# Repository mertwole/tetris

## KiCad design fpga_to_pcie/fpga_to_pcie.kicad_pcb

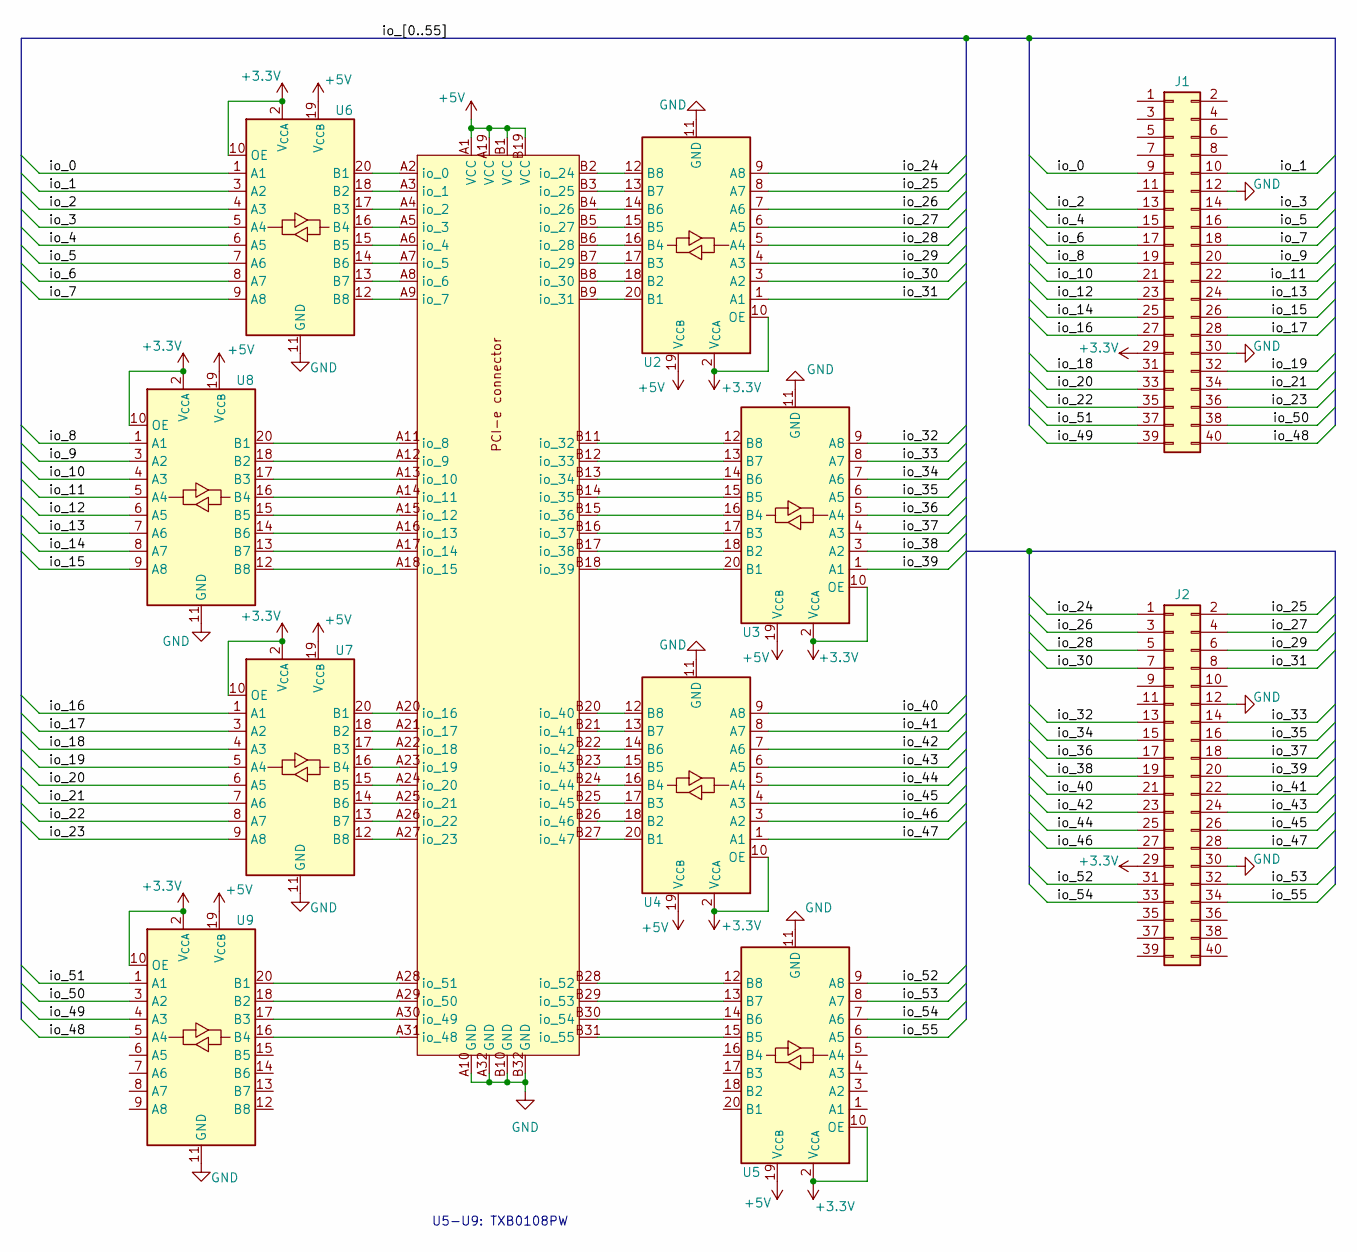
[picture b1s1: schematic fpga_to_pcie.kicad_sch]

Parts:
J1, J2: Conn_02x20_Odd_Even; IDC-Header_2x20_P2.54mm_Vertical
U1: BUS_PCIexpress_x4
U2, U3, U4, U5, U6, U7, U8, U9: TXB0108PW; TSSOP-20_4.4x6.5mm_P0.65mm

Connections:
+3.3V: J1.29, J2.29, U2.2 (V_{CCA}), U2.10 (OE), U3.2 (V_{CCA}), U3.10 (OE), U4.2 (V_{CCA}), U4.10 (OE), U5.2 (V_{CCA}), U5.10 (OE), U6.2 (V_{CCA}), U6.10 (OE), U7.2 (V_{CCA}), U7.10 (OE), U8.2 (V_{CCA}), U8.10 (OE), U9.2 (V_{CCA}), U9.10 (OE)
+5V: U1.A1 (VCC), U1.A19 (VCC), U1.B1 (VCC), U1.B19 (VCC), U2.19 (V_{CCB}), U3.19 (V_{CCB}), U4.19 (V_{CCB}), U5.19 (V_{CCB}), U6.19 (V_{CCB}), U7.19 (V_{CCB}), U8.19 (V_{CCB}), U9.19 (V_{CCB})
/io_0: J1.9, U6.1 (A1)
/io_1: J1.10, U6.3 (A2)
/io_2: J1.13, U6.4 (A3)
/io_3: J1.14, U6.5 (A4)
/io_4: J1.15, U6.6 (A5)
/io_5: J1.16, U6.7 (A6)
/io_6: J1.17, U6.8 (A7)
/io_7: J1.18, U6.9 (A8)
/io_8: J1.19, U8.1 (A1)
/io_9: J1.20, U8.3 (A2)
/io_10: J1.21, U8.4 (A3)
/io_11: J1.22, U8.5 (A4)
/io_12: J1.23, U8.6 (A5)
/io_13: J1.24, U8.7 (A6)
/io_14: J1.25, U8.8 (A7)
/io_15: J1.26, U8.9 (A8)
/io_16: J1.27, U7.1 (A1)
/io_17: J1.28, U7.3 (A2)
/io_18: J1.31, U7.4 (A3)
/io_19: J1.32, U7.5 (A4)
/io_20: J1.33, U7.6 (A5)
/io_21: J1.34, U7.7 (A6)
/io_22: J1.35, U7.8 (A7)
/io_23: J1.36, U7.9 (A8)
/io_24: J2.1, U2.9 (A8)
/io_25: J2.2, U2.8 (A7)
/io_26: J2.3, U2.7 (A6)
/io_27: J2.4, U2.6 (A5)
/io_28: J2.5, U2.5 (A4)
/io_29: J2.6, U2.4 (A3)
/io_30: J2.7, U2.3 (A2)
/io_31: J2.8, U2.1 (A1)
/io_32: J2.13, U3.9 (A8)
/io_33: J2.14, U3.8 (A7)
/io_34: J2.15, U3.7 (A6)
/io_35: J2.16, U3.6 (A5)
/io_36: J2.17, U3.5 (A4)
/io_37: J2.18, U3.4 (A3)
/io_38: J2.19, U3.3 (A2)
/io_39: J2.20, U3.1 (A1)
/io_40: J2.21, U4.9 (A8)
/io_41: J2.22, U4.8 (A7)
/io_42: J2.23, U4.7 (A6)
/io_43: J2.24, U4.6 (A5)
/io_44: J2.25, U4.5 (A4)
/io_45: J2.26, U4.4 (A3)
/io_46: J2.27, U4.3 (A2)
/io_47: J2.28, U4.1 (A1)
/io_48: J1.40, U9.5 (A4)
/io_49: J1.39, U9.4 (A3)
/io_50: J1.38, U9.3 (A2)
/io_51: J1.37, U9.1 (A1)
/io_52: J2.31, U5.9 (A8)
/io_53: J2.32, U5.8 (A7)
/io_54: J2.33, U5.7 (A6)
/io_55: J2.34, U5.6 (A5)
GND: J1.12, J1.30, J2.12, J2.30, U1.A10 (GND), U1.A32 (GND), U1.B10 (GND), U1.B32 (GND), U2.11 (GND), U3.11 (GND), U4.11 (GND), U5.11 (GND), U6.11 (GND), U7.11 (GND), U8.11 (GND), U9.11 (GND)
unnamed: U1.A2 (io_0), U6.20 (B1)
unnamed: U1.A3 (io_1), U6.18 (B2)
unnamed: U1.A4 (io_2), U6.17 (B3)
unnamed: U1.A5 (io_3), U6.16 (B4)
unnamed: U1.A6 (io_4), U6.15 (B5)
unnamed: U1.A7 (io_5), U6.14 (B6)
unnamed: U1.A8 (io_6), U6.13 (B7)
unnamed: U1.A9 (io_7), U6.12 (B8)
unnamed: U1.A11 (io_8), U8.20 (B1)
unnamed: U1.A12 (io_9), U8.18 (B2)
unnamed: U1.A13 (io_10), U8.17 (B3)
unnamed: U1.A14 (io_11), U8.16 (B4)
unnamed: U1.A15 (io_12), U8.15 (B5)
unnamed: U1.A16 (io_13), U8.14 (B6)
unnamed: U1.A17 (io_14), U8.13 (B7)
unnamed: U1.A18 (io_15), U8.12 (B8)
unnamed: U1.A20 (io_16), U7.20 (B1)
unnamed: U1.A21 (io_17), U7.18 (B2)
unnamed: U1.A22 (io_18), U7.17 (B3)
unnamed: U1.A23 (io_19), U7.16 (B4)
unnamed: U1.A24 (io_20), U7.15 (B5)
unnamed: U1.A25 (io_21), U7.14 (B6)
unnamed: U1.A26 (io_22), U7.13 (B7)
unnamed: U1.A27 (io_23), U7.12 (B8)
unnamed: U1.B2 (io_24), U2.12 (B8)
unnamed: U1.B3 (io_25), U2.13 (B7)
unnamed: U1.B4 (io_26), U2.14 (B6)
unnamed: U1.B5 (io_27), U2.15 (B5)
unnamed: U1.B6 (io_28), U2.16 (B4)
unnamed: U1.B7 (io_29), U2.17 (B3)
unnamed: U1.B8 (io_30), U2.18 (B2)
unnamed: U1.B9 (io_31), U2.20 (B1)
unnamed: U1.B11 (io_32), U3.12 (B8)
unnamed: U1.B12 (io_33), U3.13 (B7)
unnamed: U1.B13 (io_34), U3.14 (B6)
unnamed: U1.B14 (io_35), U3.15 (B5)
unnamed: U1.B15 (io_36), U3.16 (B4)
unnamed: U1.B16 (io_37), U3.17 (B3)
unnamed: U1.B17 (io_38), U3.18 (B2)
unnamed: U1.B18 (io_39), U3.20 (B1)
unnamed: U1.B20 (io_40), U4.12 (B8)
unnamed: U1.B21 (io_41), U4.13 (B7)
unnamed: U1.B22 (io_42), U4.14 (B6)
unnamed: U1.B23 (io_43), U4.15 (B5)
unnamed: U1.B24 (io_44), U4.16 (B4)
unnamed: U1.B25 (io_45), U4.17 (B3)
unnamed: U1.B26 (io_46), U4.18 (B2)
unnamed: U1.B27 (io_47), U4.20 (B1)
unnamed: U1.A31 (io_48), U9.16 (B4)
unnamed: U1.A30 (io_49), U9.17 (B3)
unnamed: U1.A29 (io_50), U9.18 (B2)
unnamed: U1.A28 (io_51), U9.20 (B1)
unnamed: U1.B28 (io_52), U5.12 (B8)
unnamed: U1.B29 (io_53), U5.13 (B7)
unnamed: U1.B30 (io_54), U5.14 (B6)
unnamed: U1.B31 (io_55), U5.15 (B5)

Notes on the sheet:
U5-U9: TXB0108PW

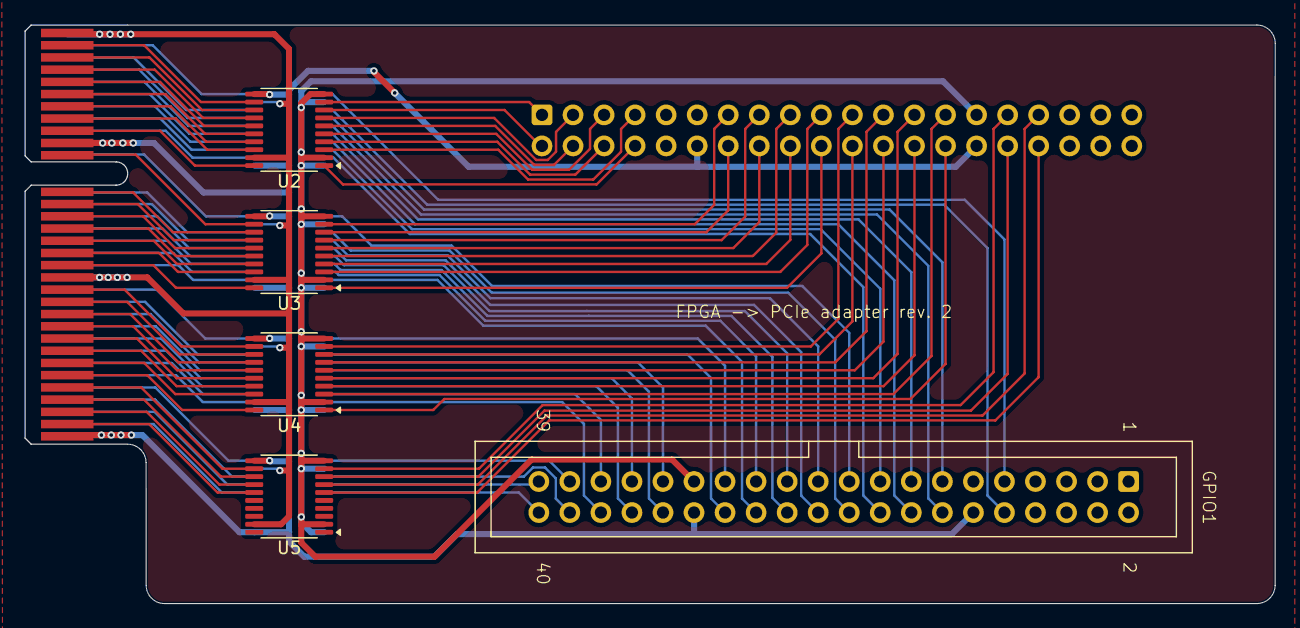
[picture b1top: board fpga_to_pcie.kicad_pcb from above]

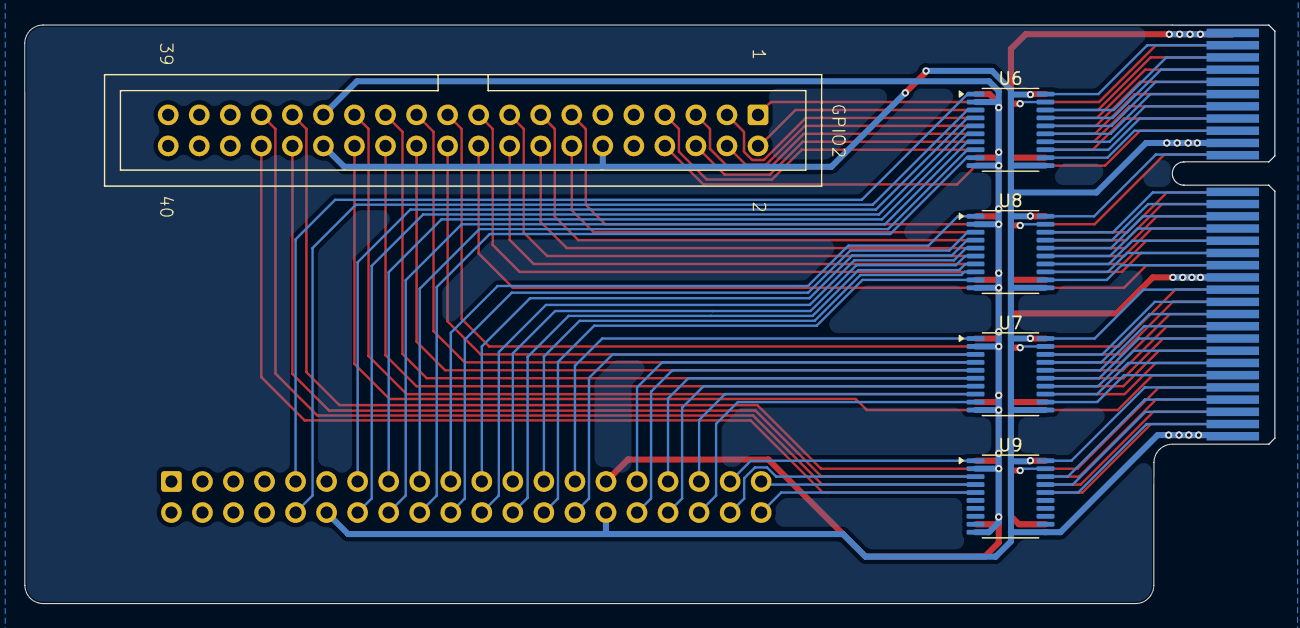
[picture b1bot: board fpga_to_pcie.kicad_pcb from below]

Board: 2 copper layers, 102.3 x 47.3 mm, 11 parts (5 on the bottom side), 115 nets.

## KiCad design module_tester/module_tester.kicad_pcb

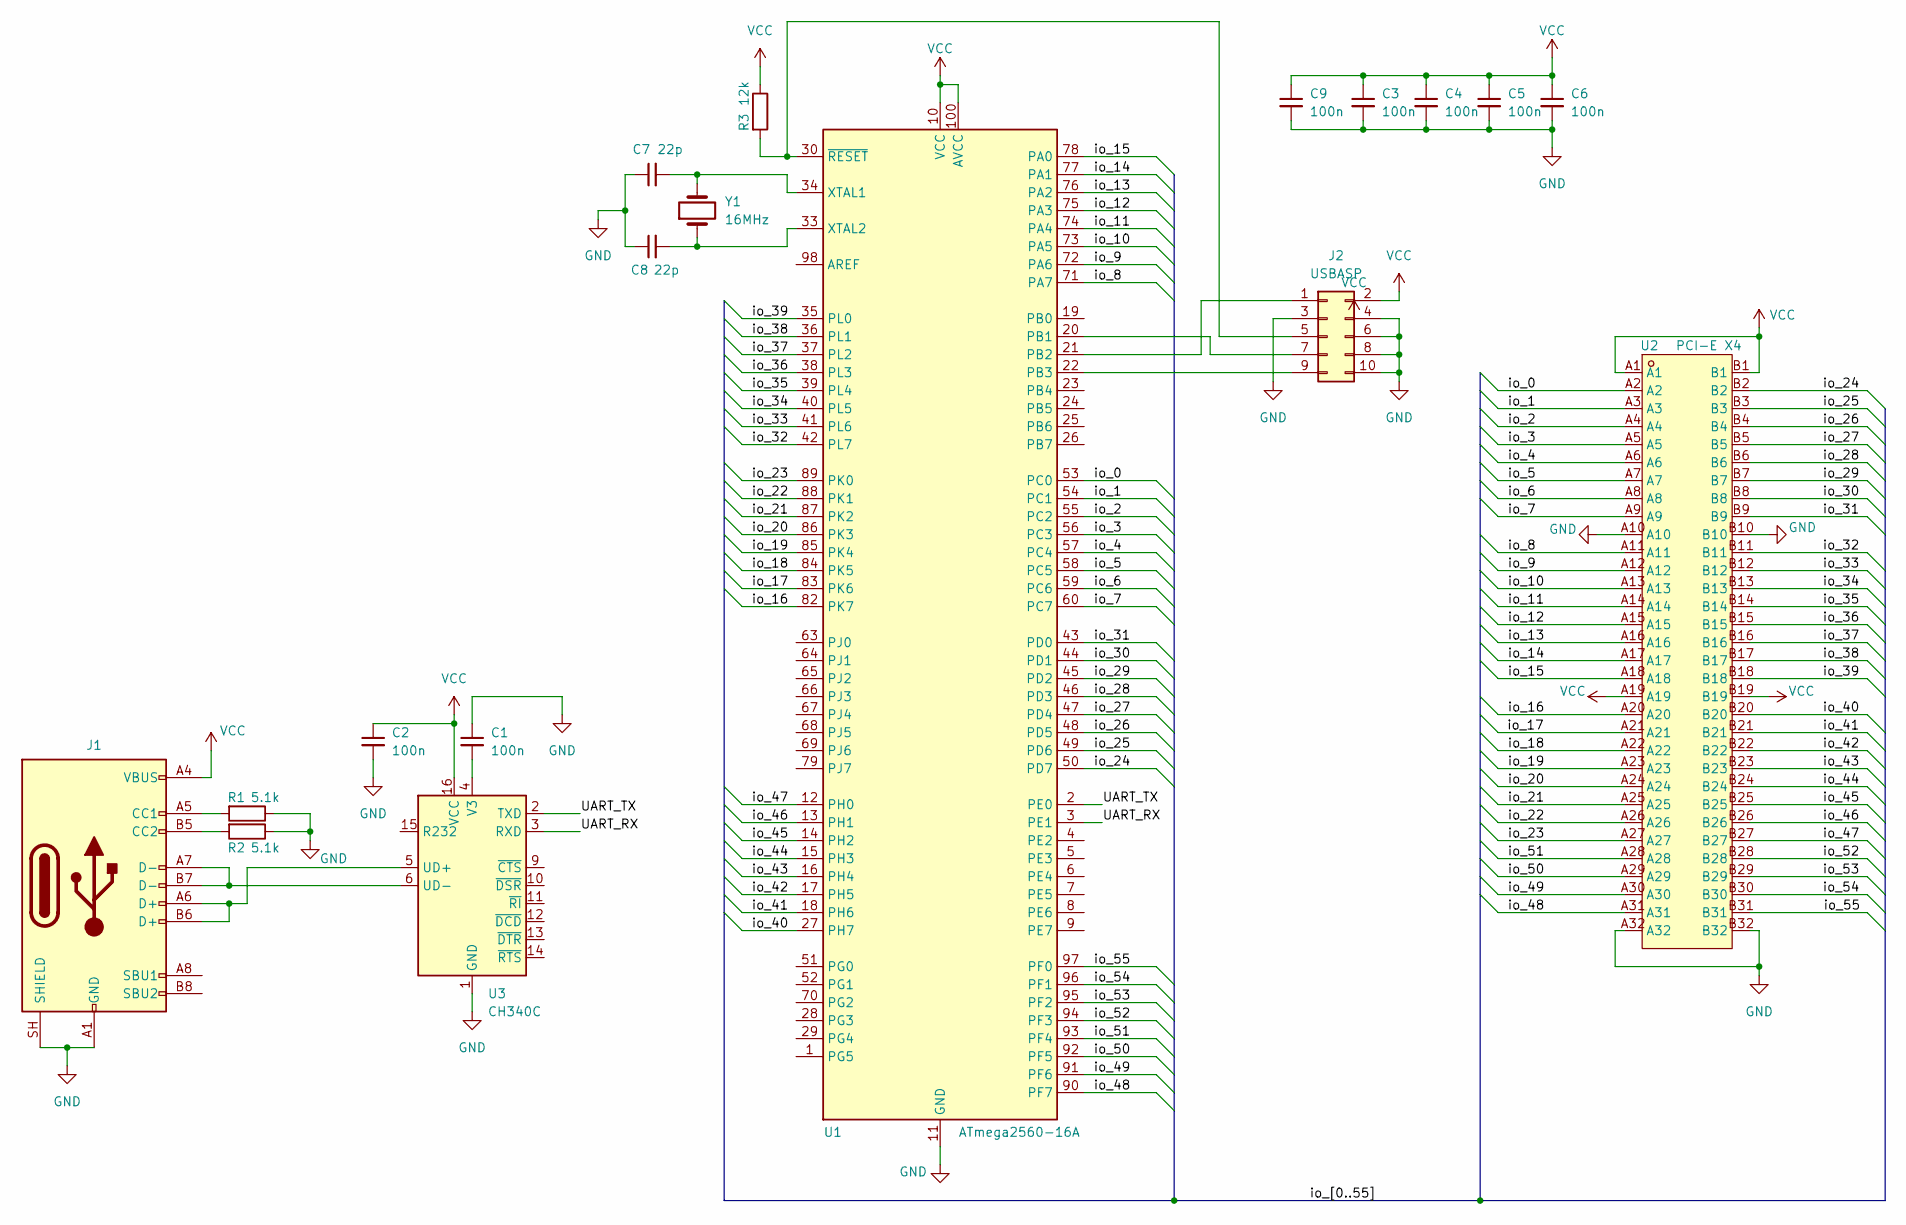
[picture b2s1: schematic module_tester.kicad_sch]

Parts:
C1, C2, C3, C4, C5, C6, C9: 100n; C_0603_1608Metric
C7, C8: 22p; C_0603_1608Metric
J1: USB_C_Receptacle_USB2.0_16P; USB_C_Receptacle_G-Switch_GT-USB-7010ASV
J2: USBASP; IDC-Header_2x05_P2.54mm_Vertical
R1, R2: 5.1k; R_1206_3216Metric
R3: 12k; R_1206_3216Metric
U1: ATmega2560-16A; TQFP-100_14x14mm_P0.5mm
U2: PCI-E X4; PCI-E X4 Socket; MPN 2EG03227-D2D-DF; LCSC Part C2832353
U3: CH340C; SOIC-16_3.9x9.9mm_P1.27mm
Y1: 16MHz; Crystal_SMD_HC49-SD_HandSoldering

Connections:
/UART_RX: U1.3 (PE1), U3.3 (RXD)
/UART_TX: U1.2 (PE0), U3.2 (TXD)
/io_0: U1.53 (PC0), U2.A2
/io_1: U1.54 (PC1), U2.A3
/io_2: U1.55 (PC2), U2.A4
/io_3: U1.56 (PC3), U2.A5
/io_4: U1.57 (PC4), U2.A6
/io_5: U1.58 (PC5), U2.A7
/io_6: U1.59 (PC6), U2.A8
/io_7: U1.60 (PC7), U2.A9
/io_8: U1.71 (PA7), U2.A11
/io_9: U1.72 (PA6), U2.A12
/io_10: U1.73 (PA5), U2.A13
/io_11: U1.74 (PA4), U2.A14
/io_12: U1.75 (PA3), U2.A15
/io_13: U1.76 (PA2), U2.A16
/io_14: U1.77 (PA1), U2.A17
/io_15: U1.78 (PA0), U2.A18
/io_16: U1.82 (PK7), U2.A20
/io_17: U1.83 (PK6), U2.A21
/io_18: U1.84 (PK5), U2.A22
/io_19: U1.85 (PK4), U2.A23
/io_20: U1.86 (PK3), U2.A24
/io_21: U1.87 (PK2), U2.A25
/io_22: U1.88 (PK1), U2.A26
/io_23: U1.89 (PK0), U2.A27
/io_24: U1.50 (PD7), U2.B2
/io_25: U1.49 (PD6), U2.B3
/io_26: U1.48 (PD5), U2.B4
/io_27: U1.47 (PD4), U2.B5
/io_28: U1.46 (PD3), U2.B6
/io_29: U1.45 (PD2), U2.B7
/io_30: U1.44 (PD1), U2.B8
/io_31: U1.43 (PD0), U2.B9
/io_32: U1.42 (PL7), U2.B11
/io_33: U1.41 (PL6), U2.B12
/io_34: U1.40 (PL5), U2.B13
/io_35: U1.39 (PL4), U2.B14
/io_36: U1.38 (PL3), U2.B15
/io_37: U1.37 (PL2), U2.B16
/io_38: U1.36 (PL1), U2.B17
/io_39: U1.35 (PL0), U2.B18
/io_40: U1.27 (PH7), U2.B20
/io_41: U1.18 (PH6), U2.B21
/io_42: U1.17 (PH5), U2.B22
/io_43: U1.16 (PH4), U2.B23
/io_44: U1.15 (PH3), U2.B24
/io_45: U1.14 (PH2), U2.B25
/io_46: U1.13 (PH1), U2.B26
/io_47: U1.12 (PH0), U2.B27
/io_48: U1.90 (PF7), U2.A31
/io_49: U1.91 (PF6), U2.A30
/io_50: U1.92 (PF5), U2.A29
/io_51: U1.93 (PF4), U2.A28
/io_52: U1.94 (PF3), U2.B28
/io_53: U1.95 (PF2), U2.B29
/io_54: U1.96 (PF1), U2.B30
/io_55: U1.97 (PF0), U2.B31
GND: C1.1, C2.2, C3.2, C4.2, C5.2, C6.2, C7.1, C8.1, C9.2, J1.A1 (GND), J1.A12 (GND), J1.B1 (GND), J1.B12 (GND), J1.SH (SHIELD), J2.3, J2.4, J2.6, J2.8, J2.10, R1.1, R2.1, U1.11 (GND), U1.32 (GND), U1.62 (GND), U1.81 (GND), U1.99 (GND), U2.A10, U2.A32, U2.B10, U2.B32, U3.1 (GND)
unnamed: J1.A5 (CC1), R1.2
unnamed: J1.B5 (CC2), R2.2
unnamed: J2.1, U1.21 (PB2)
unnamed: J2.5, R3.2, U1.30 (~RESET)
unnamed: J2.7, U1.20 (PB1)
unnamed: J2.9, U1.22 (PB3)
unnamed: C7.2, U1.34 (XTAL1), Y1.2
unnamed: C8.2, U1.33 (XTAL2), Y1.1
unnamed: J1.A6 (D+), J1.B6 (D+), U3.5 (UD+)
unnamed: J1.A7 (D-), J1.B7 (D-), U3.6 (UD-)
unnamed: C1.2, U3.4 (V3)
VCC: C2.1, C3.1, C4.1, C5.1, C6.1, C9.1, J1.A4 (VBUS), J1.A9 (VBUS), J1.B4 (VBUS), J1.B9 (VBUS), J2.2, R3.1, U1.10 (VCC), U1.31 (VCC), U1.61 (VCC), U1.80 (VCC), U1.100 (AVCC), U2.A1, U2.A19, U2.B1, U2.B19, U3.16 (VCC)

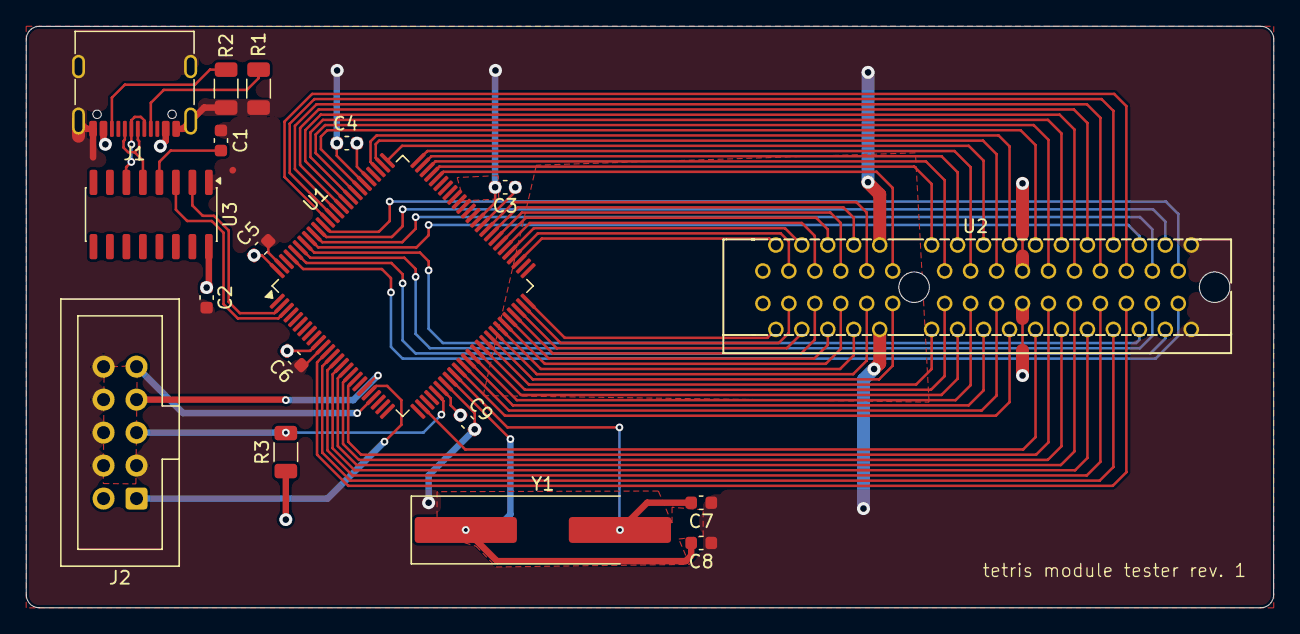
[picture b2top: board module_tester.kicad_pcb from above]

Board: 2 copper layers, 96.1 x 44.8 mm, 18 parts (0 on the bottom side), 71 nets.
